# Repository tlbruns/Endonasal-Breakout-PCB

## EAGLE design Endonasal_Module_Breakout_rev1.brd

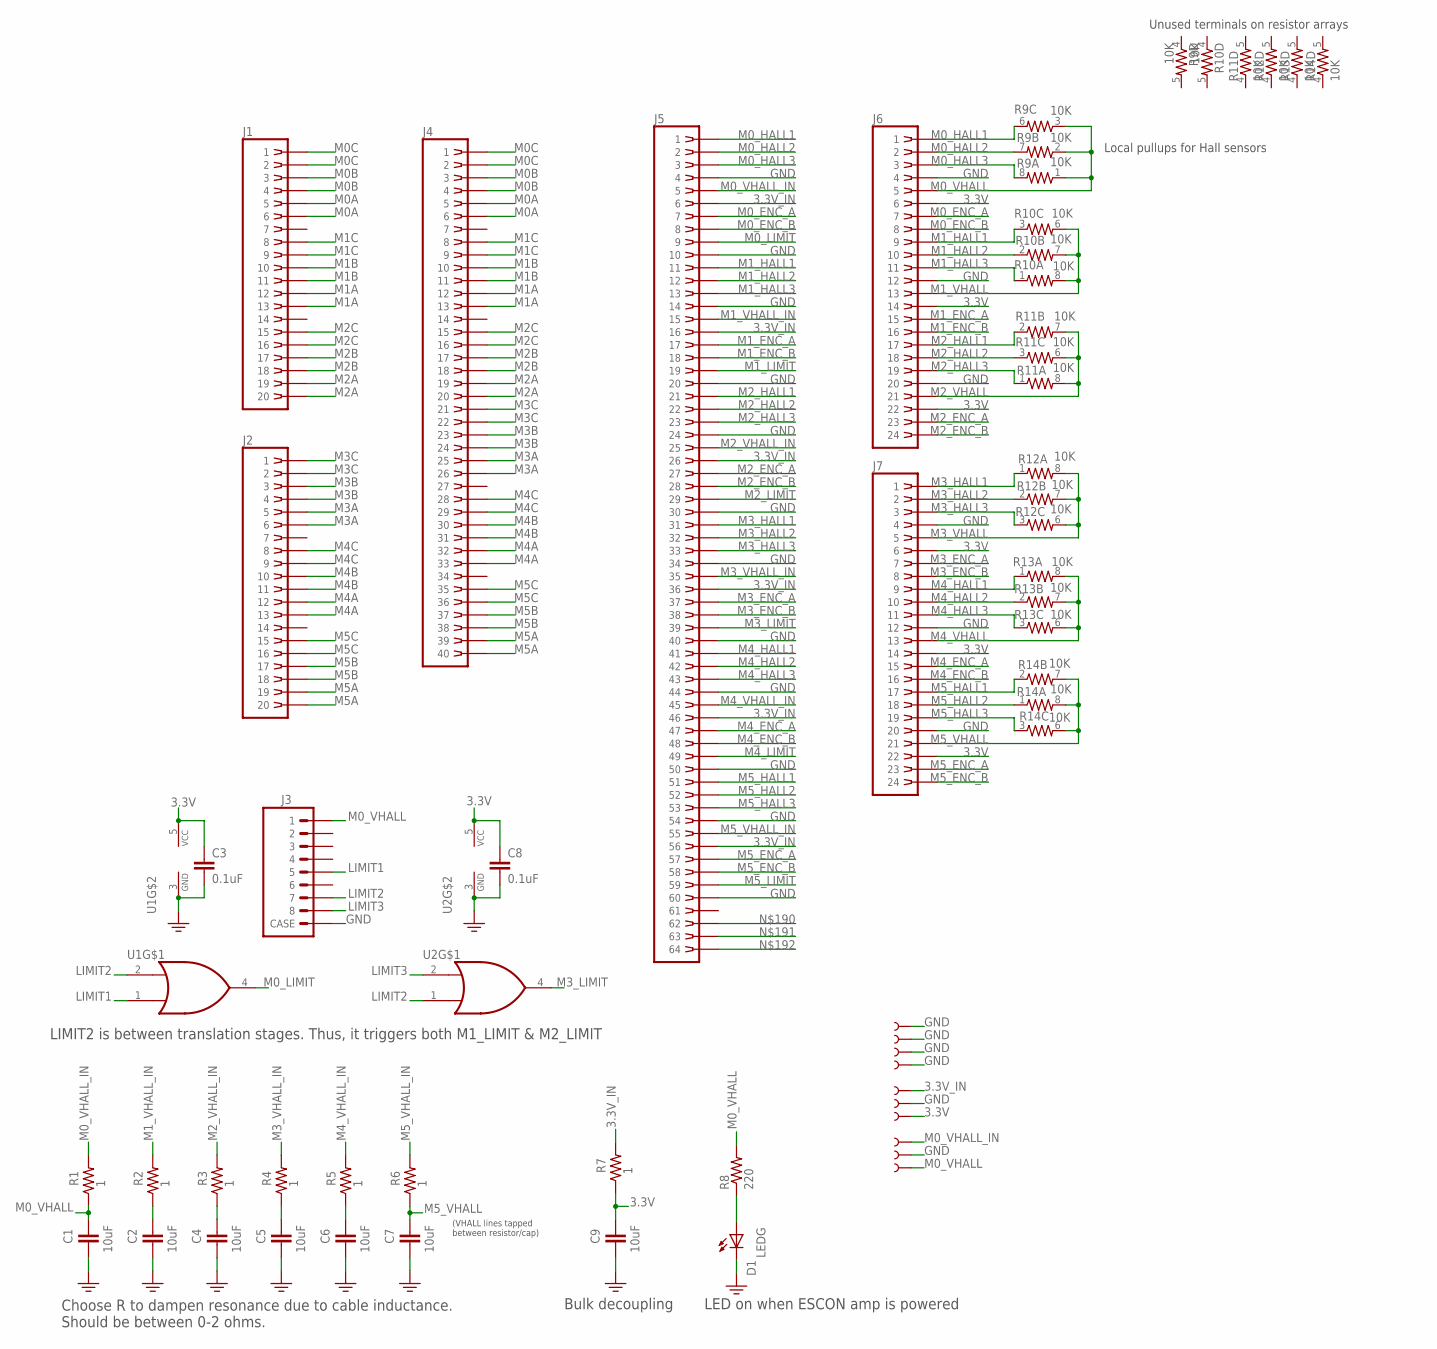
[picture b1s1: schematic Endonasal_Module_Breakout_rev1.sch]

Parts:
3.3V, 3.3V-IN, 5V, 5V-IN: TEST-POINT_5021
C1, C2, C4, C5, C6, C7, C9: 10uF; C0805K
C3, C8: 0.1uF; 0603-CAP
D1: LEDG; LED-0805
GND: TEST-POINT_5021
J1, J2: CONN_RECT_2X10TH; CONN_IDC_20_MALE_TH
J3: JACK_8P8C_RJ45_ETHERNET; ETHERNET_A104932
J4: CONN_RECT_2X20TH; CONN_IDC_40_MALE_TH
J5: CONN_RECT_2X32NOHOLES; CONN_IDC_64_MALE_TH_NOHOLES
J6, J7: CONN_RECT_2X12TH; CONN_IDC_24_MALE_TH
R1, R2, R3, R4, R5, R6, R7: 1; 0603-RES
R8: 220; 0603-RES
R9, R10, R11, R12, R13, R14: 10K; 0603-ARV
TP5: TEST-POINT_5021
TP7, TP8, TP9, TP10: TEST-POINT3X5; PAD.03X.05
U1: OR_M0; SOT353
U2: OR_M3; SOT353

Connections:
3.3V: 3.3V.P$1, C3.1, C8.1, C9.1, J6.P$6 (6), J6.P$14 (14), J6.P$22 (22), J7.P$6 (6), J7.P$14 (14), J7.P$22 (22), R7.1, U1.5 (VCC), U2.5 (VCC)
3.3V_IN: 3.3V-IN.P$1, J5.P$6 (6), J5.P$16 (16), J5.P$26 (26), J5.P$36 (36), J5.P$46 (46), J5.P$56 (56), R7.2
GND: C1.2, C2.2, C3.2, C4.2, C5.2, C6.2, C7.2, C8.2, C9.2, D1.C, GND.P$1, J3.SHIELD1 (CASE), J3.SHIELD2 (CASE), J5.P$4 (4), J5.P$10 (10), J5.P$14 (14), J5.P$20 (20), J5.P$24 (24), J5.P$30 (30), J5.P$34 (34), J5.P$40 (40), J5.P$44 (44), J5.P$50 (50), J5.P$54 (54), J5.P$60 (60), J6.P$4 (4), J6.P$12 (12), J6.P$20 (20), J7.P$4 (4), J7.P$12 (12), J7.P$20 (20), TP5.P$1, TP7.P$1, TP8.P$1, TP9.P$1, TP10.P$1, U1.3 (GND), U2.3 (GND)
LIMIT1: J3.P$5 (5), U1.1 (B)
LIMIT2: J3.P$7 (7), U1.2 (A), U2.1 (B)
LIMIT3: J3.P$8 (8), U2.2 (A)
M0A: J1.P$5 (5), J1.P$6 (6), J4.P$5 (5), J4.P$6 (6)
M0B: J1.P$3 (3), J1.P$4 (4), J4.P$3 (3), J4.P$4 (4)
M0C: J1.P$1 (1), J1.P$2 (2), J4.P$1 (1), J4.P$2 (2)
M0_ENC_A: J5.P$7 (7), J6.P$7 (7)
M0_ENC_B: J5.P$8 (8), J6.P$8 (8)
M0_HALL1: J5.P$1 (1), J6.P$1 (1), R9.6 (2)
M0_HALL2: J5.P$2 (2), J6.P$2 (2), R9.7 (2)
M0_HALL3: J5.P$3 (3), J6.P$3 (3), R9.8 (2)
M0_LIMIT: J5.P$9 (9), U1.4 (Y)
M0_VHALL: 5V.P$1, C1.1, J3.P$1 (1), J6.P$5 (5), R1.1, R8.2, R9.1, R9.2 (1), R9.3 (1)
M0_VHALL_IN: 5V-IN.P$1, J5.P$5 (5), R1.2
M1A: J1.P$12 (12), J1.P$13 (13), J4.P$12 (12), J4.P$13 (13)
M1B: J1.P$10 (10), J1.P$11 (11), J4.P$10 (10), J4.P$11 (11)
M1C: J1.P$8 (8), J1.P$9 (9), J4.P$8 (8), J4.P$9 (9)
M1_ENC_A: J5.P$17 (17), J6.P$15 (15)
M1_ENC_B: J5.P$18 (18), J6.P$16 (16)
M1_HALL1: J5.P$11 (11), J6.P$9 (9), R10.3 (1)
M1_HALL2: J5.P$12 (12), J6.P$10 (10), R10.2 (1)
M1_HALL3: J5.P$13 (13), J6.P$11 (11), R10.1
M1_LIMIT: J5.P$19 (19)
M1_VHALL: C2.1, J6.P$13 (13), R2.1, R10.6 (2), R10.7 (2), R10.8 (2)
M1_VHALL_IN: J5.P$15 (15), R2.2
M2A: J1.P$19 (19), J1.P$20 (20), J4.P$19 (19), J4.P$20 (20)
M2B: J1.P$17 (17), J1.P$18 (18), J4.P$17 (17), J4.P$18 (18)
M2C: J1.P$15 (15), J1.P$16 (16), J4.P$15 (15), J4.P$16 (16)
M2_ENC_A: J5.P$27 (27), J6.P$23 (23)
M2_ENC_B: J5.P$28 (28), J6.P$24 (24)
M2_HALL1: J5.P$21 (21), J6.P$17 (17), R11.2 (1)
M2_HALL2: J5.P$22 (22), J6.P$18 (18), R11.3 (1)
M2_HALL3: J5.P$23 (23), J6.P$19 (19), R11.1
M2_LIMIT: J5.P$29 (29)
M2_VHALL: C4.1, J6.P$21 (21), R3.1, R11.6 (2), R11.7 (2), R11.8 (2)
M2_VHALL_IN: J5.P$25 (25), R3.2
M3A: J2.P$5 (5), J2.P$6 (6), J4.P$25 (25), J4.P$26 (26)
M3B: J2.P$3 (3), J2.P$4 (4), J4.P$23 (23), J4.P$24 (24)
M3C: J2.P$1 (1), J2.P$2 (2), J4.P$21 (21), J4.P$22 (22)
M3_ENC_A: J5.P$37 (37), J7.P$7 (7)
M3_ENC_B: J5.P$38 (38), J7.P$8 (8)
M3_HALL1: J5.P$31 (31), J7.P$1 (1), R12.1
M3_HALL2: J5.P$32 (32), J7.P$2 (2), R12.2 (1)
M3_HALL3: J5.P$33 (33), J7.P$3 (3), R12.3 (1)
M3_LIMIT: J5.P$39 (39), U2.4 (Y)
M3_VHALL: C5.1, J7.P$5 (5), R4.1, R12.6 (2), R12.7 (2), R12.8 (2)
M3_VHALL_IN: J5.P$35 (35), R4.2
M4A: J2.P$12 (12), J2.P$13 (13), J4.P$32 (32), J4.P$33 (33)
M4B: J2.P$10 (10), J2.P$11 (11), J4.P$30 (30), J4.P$31 (31)
M4C: J2.P$8 (8), J2.P$9 (9), J4.P$28 (28), J4.P$29 (29)
M4_ENC_A: J5.P$47 (47), J7.P$15 (15)
M4_ENC_B: J5.P$48 (48), J7.P$16 (16)
M4_HALL1: J5.P$41 (41), J7.P$9 (9), R13.1
M4_HALL2: J5.P$42 (42), J7.P$10 (10), R13.2 (1)
M4_HALL3: J5.P$43 (43), J7.P$11 (11), R13.3 (1)
M4_LIMIT: J5.P$49 (49)
M4_VHALL: C6.1, J7.P$13 (13), R5.1, R13.6 (2), R13.7 (2), R13.8 (2)
M4_VHALL_IN: J5.P$45 (45), R5.2
M5A: J2.P$19 (19), J2.P$20 (20), J4.P$39 (39), J4.P$40 (40)
M5B: J2.P$17 (17), J2.P$18 (18), J4.P$37 (37), J4.P$38 (38)
M5C: J2.P$15 (15), J2.P$16 (16), J4.P$35 (35), J4.P$36 (36)
M5_ENC_A: J5.P$57 (57), J7.P$23 (23)
M5_ENC_B: J5.P$58 (58), J7.P$24 (24)
M5_HALL1: J5.P$51 (51), J7.P$17 (17), R14.2 (1)
M5_HALL2: J5.P$52 (52), J7.P$18 (18), R14.1
M5_HALL3: J5.P$53 (53), J7.P$19 (19), R14.3 (1)
M5_LIMIT: J5.P$59 (59)
M5_VHALL: C7.1, J7.P$21 (21), R6.1, R14.6 (2), R14.7 (2), R14.8 (2)
M5_VHALL_IN: J5.P$55 (55), R6.2
unnamed: D1.A, R8.1

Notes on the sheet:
LED on when ESCON amp is powered
LIMIT2 is between translation stages. Thus, it triggers both M1_LIMIT & M2_LIMIT
Choose R to dampen resonance due to cable inductance. Should be between 0-2 ohms.
Bulk decoupling
(VHALL lines tapped between resistor/cap)
Local pullups for Hall sensors
Unused terminals on resistor arrays

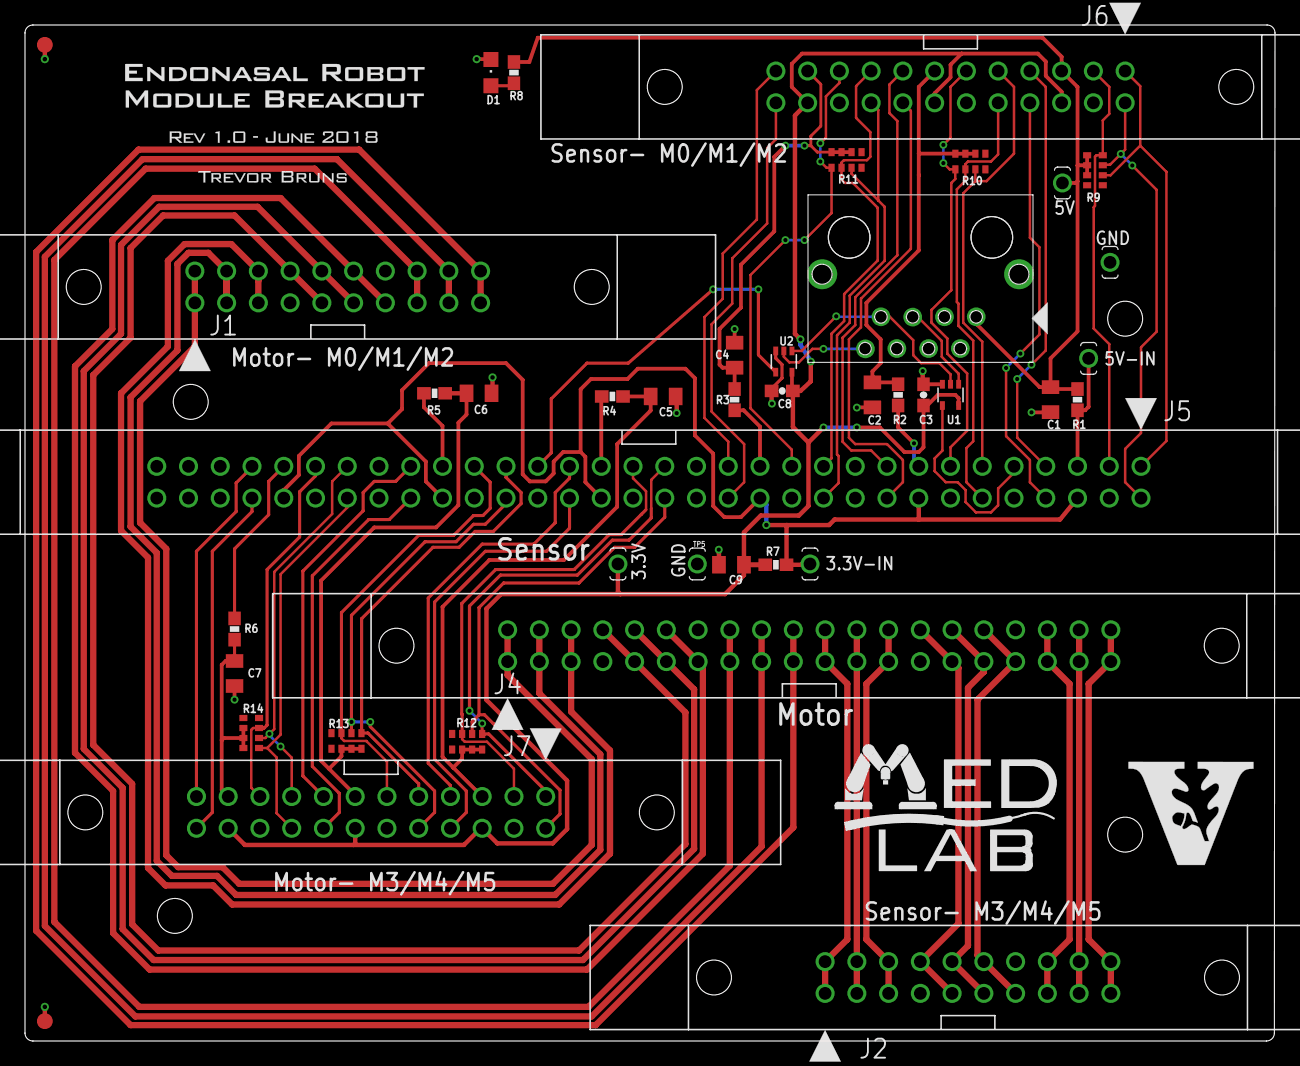
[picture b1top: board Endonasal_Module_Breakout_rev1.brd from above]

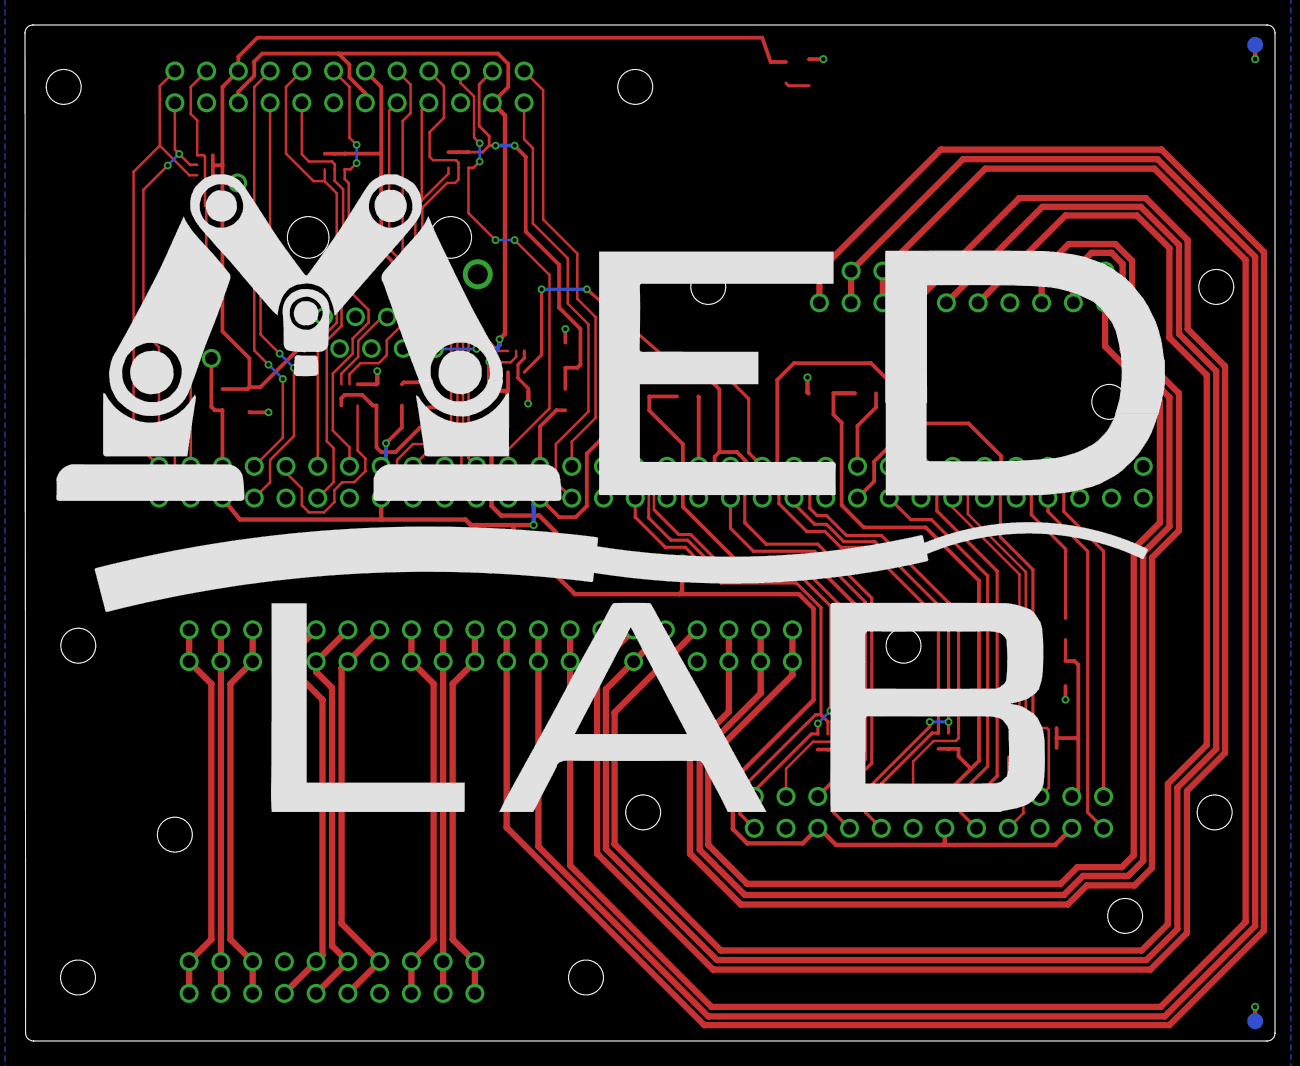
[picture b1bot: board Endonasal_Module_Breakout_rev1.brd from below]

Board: 2 copper layers, 100.0 x 81.3 mm, 47 parts (3 on the bottom side), 69 nets.

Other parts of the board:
U$1: LOGO_MEDLAB_3X2
U$2: LOGO_V_OAK
U$4: LOGO_MEDLAB_0.7X0.4
U$5: LOGO_ENDONASAL_BREAKOUT_1.0

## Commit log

2018-06-11 All traces routed
2018-06-11 Increased connector spacing
    Increased spacing between connectors to be at least 5mm
2018-06-11 Silkscreen
    Set font sizes for passives
    Renumbered components
    Created net classes for POWER and MOTOR
    Ran DRC and ERC
2018-06-12 Layout finished (hopefully)
2018-06-13 As Submitted
    Created Gerbers and submitted for manufacture

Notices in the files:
parts and their libraries:
SparkFun-Capacitors: Licensing: Creative Commons ShareAlike 4.0 International - https://creativecommons.org/licenses/by-sa/4.0
